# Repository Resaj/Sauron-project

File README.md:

# Sauron project
This video scanner module is based on David Chatting's project [Arduino Eye Shield](http://www.davidchatting.com/arduinoeyeshield/).

Our finally purpose is adapting this scanner for reading the enviroment with competition robots like line-following or minisumo robots, but applying another microcontroller with higher proccesing speed.

## Author
[Rubén Espino San José](https://github.com/Resaj)

## License

Todos estos productos están liberados mediante [Creative Commons Attribution-ShareAlike 4.0 International License](http://creativecommons.org/licenses/by-sa/4.0/).  
_All these products are released under [Creative Commons Attribution-ShareAlike 4.0 International License](http://creativecommons.org/licenses/by-sa/4.0/)._

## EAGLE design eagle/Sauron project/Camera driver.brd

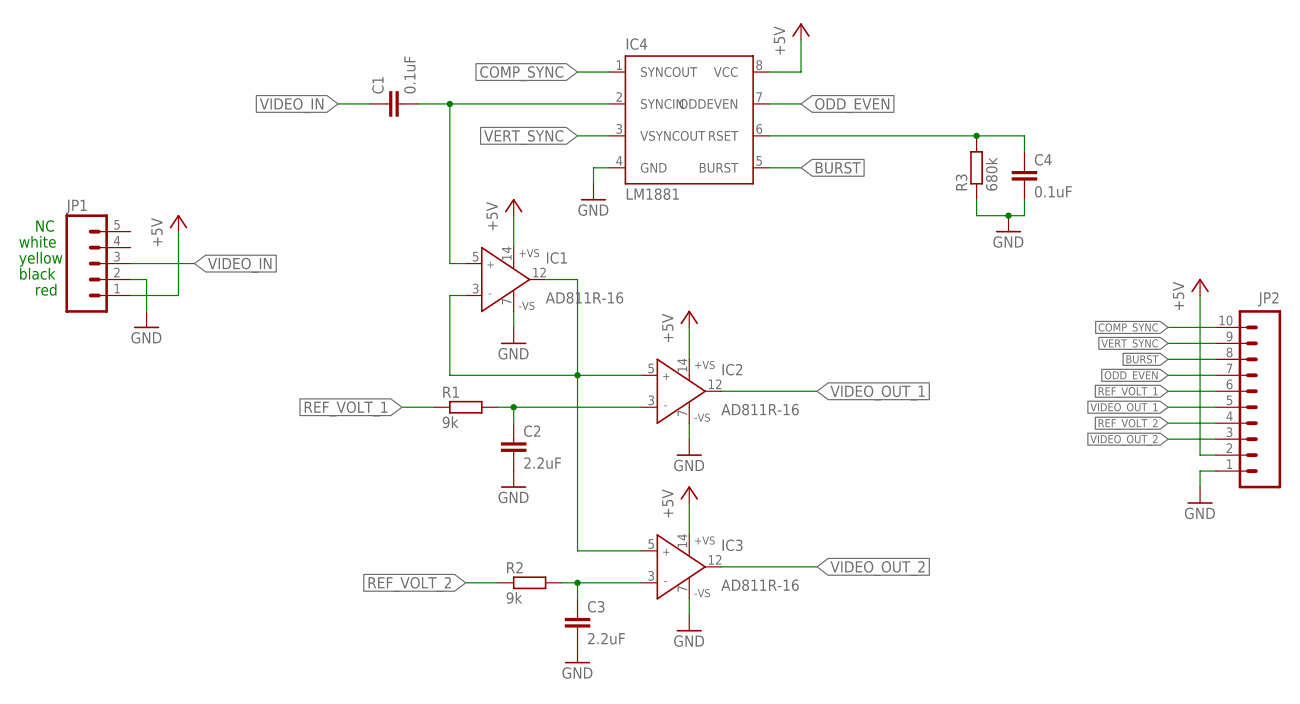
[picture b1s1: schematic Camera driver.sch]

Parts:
C1, C4: 0.1uF; C0603
C2, C3: 2.2uF; C0603
IC1, IC2, IC3: AD811R-16; SOIC16R
IC4: LM1881; DIL08
JP1: M05PTH; 1X05
JP2: M10SILK_FEMALE_PTH; 1X10
R1, R2: 9k; R0603
R3: 680k; R0603

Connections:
+5V: IC1.14 (+VS), IC2.14 (+VS), IC3.14 (+VS), IC4.8 (VCC), JP1.1, JP2.2
BURST: IC4.5 (BURST), JP2.8
COMP_SYNC: IC4.1 (SYNCOUT), JP2.10
GND: C2.2, C3.2, C4.2, IC1.7 (-VS), IC2.7 (-VS), IC3.7 (-VS), IC4.4 (GND), JP1.2, JP2.1, R3.1
unnamed: IC1.3 (IN-), IC1.12 (OUT), IC2.5 (IN+), IC3.5 (IN+)
unnamed: C4.1, IC4.6 (RSET), R3.2
unnamed: C3.1, IC3.3 (IN-), R2.2
unnamed: C1.2, IC1.5 (IN+), IC4.2 (SYNCIN)
unnamed: C2.1, IC2.3 (IN-), R1.2
ODD_EVEN: IC4.7 (ODDEVEN), JP2.7
REF_VOLT_1: JP2.6, R1.1
REF_VOLT_2: JP2.4, R2.1
VERT_SYNC: IC4.3 (VSYNCOUT), JP2.9
VIDEO_IN: C1.1, JP1.3
VIDEO_OUT_1: IC2.12 (OUT), JP2.5
VIDEO_OUT_2: IC3.12 (OUT), JP2.3

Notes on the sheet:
white
yellow
black
red

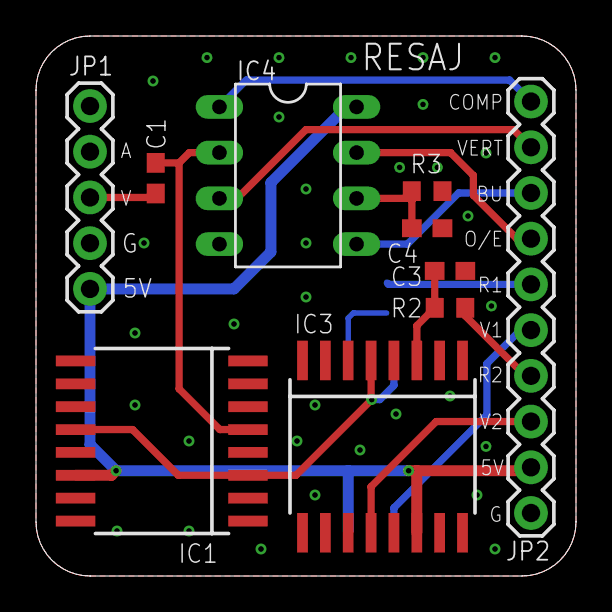
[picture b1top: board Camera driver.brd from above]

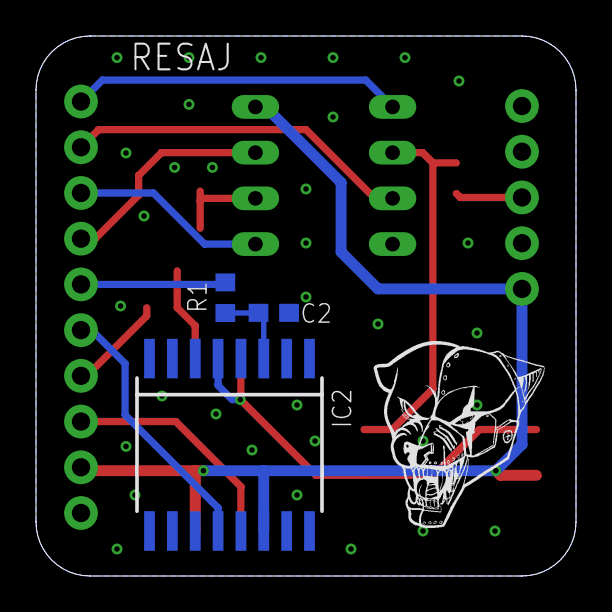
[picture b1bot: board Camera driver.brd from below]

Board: 2 copper layers, 30.0 x 30.0 mm, 14 parts (4 on the bottom side), 16 nets.

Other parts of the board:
U$1: LOGO_PUMA_10X10

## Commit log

2016-11-26 Arduino program actualized and processing interface added
2017-02-16 Led matrix added for testing
2017-07-10 Program actualized
2017-07-10 Added faster digital read

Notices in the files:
parts and their libraries:
SparkFun-Connectors: Licensing: Creative Commons ShareAlike 4.0 International - https://creativecommons.org/licenses/by-sa/4.0
